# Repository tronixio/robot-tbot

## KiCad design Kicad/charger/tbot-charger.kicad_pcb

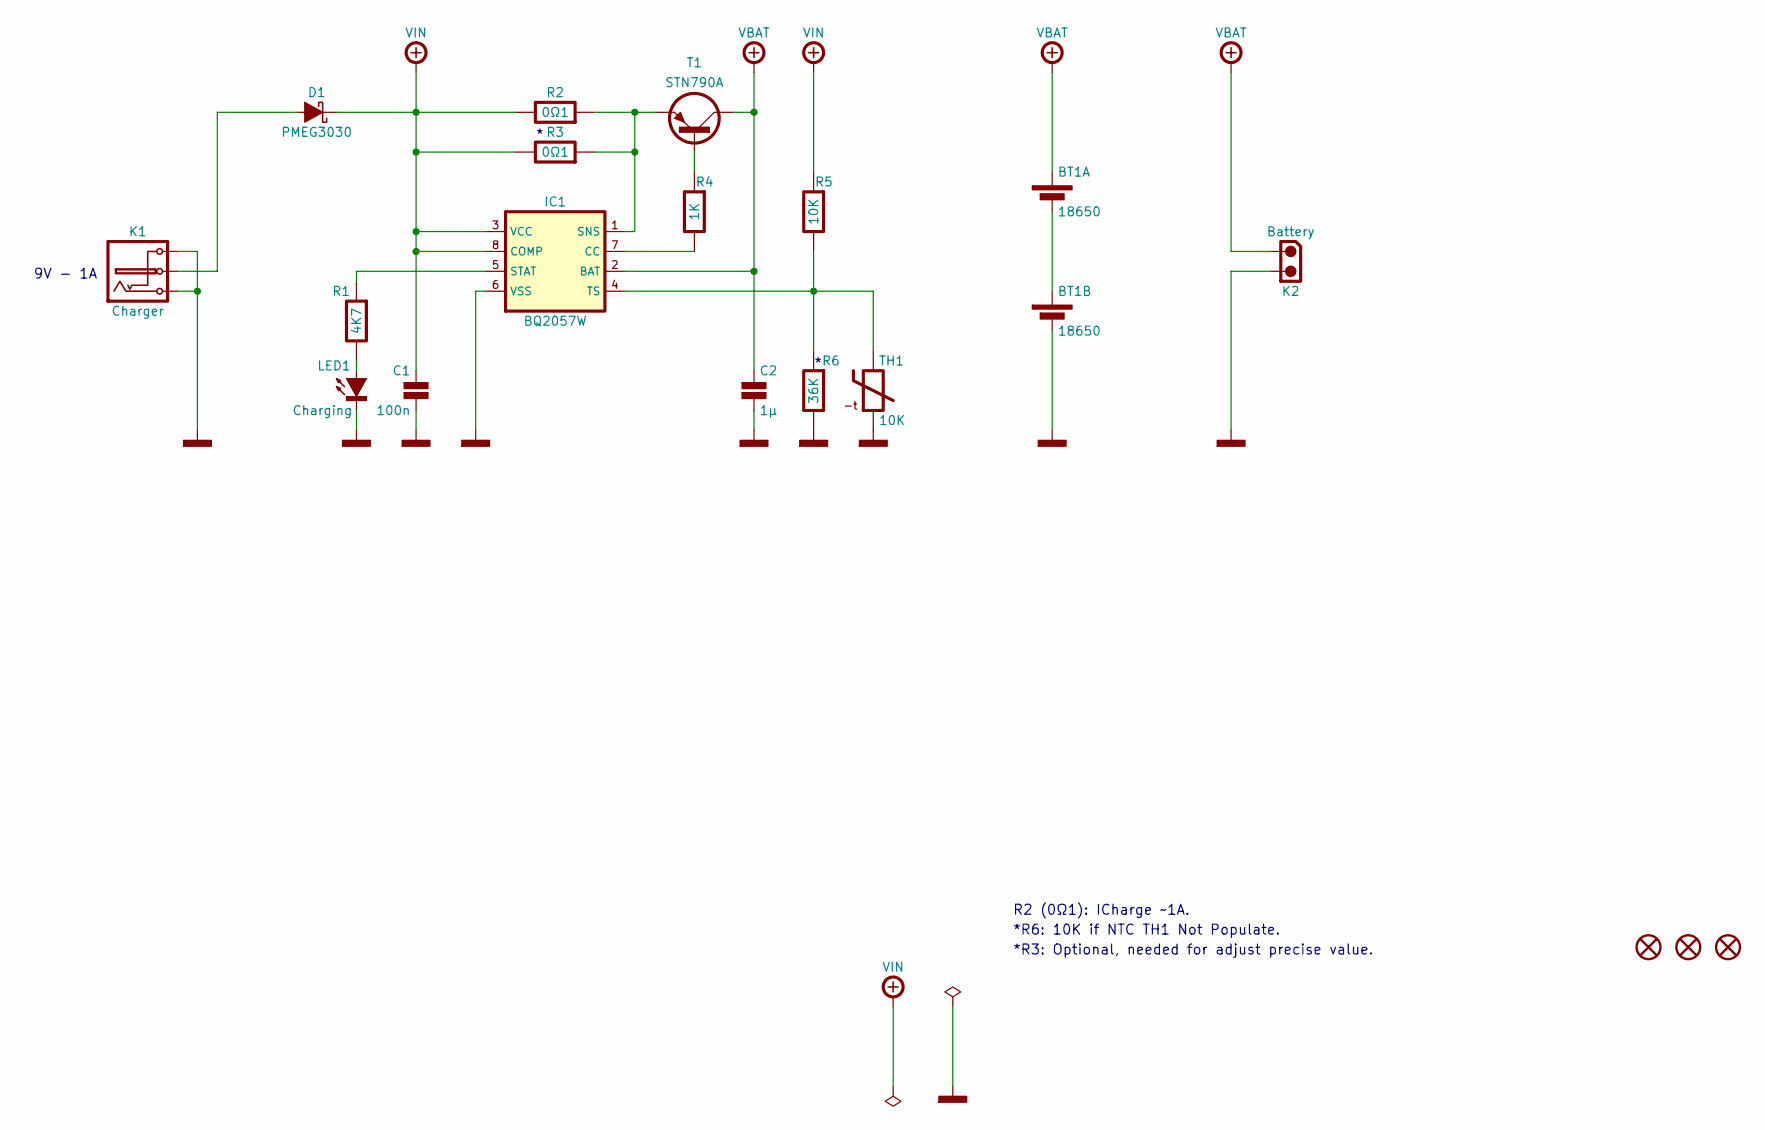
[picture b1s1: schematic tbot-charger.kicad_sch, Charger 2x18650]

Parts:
BT1: 18650; KEYSTONE-1049; MOUSER 534-1049
C1: 100n; CAPACITOR-1206
C2: 1µ; CAPACITOR-1206
D1: PMEG3030; SOD-128; MOUSER 771-PMEG3030EP115
H1, H2, H3: MOUNTING-HOLE-MASK-3MM; M3-MASK
IC1: BQ2057W; SOIC-08; MOUSER 595-BQ2057WSN
K1: Charger; CUI-PJ-102AH; MOUSER 490-PJ-102AH
K2: Battery; MOLEX-22057025; MOUSER 538-22-05-7025
LED1: Charging; LED-1206; MOUSER 604-APTR3216-VFX
R1: 4K7; RESISTOR-1206
R2, R3: 0Ω1; RESISTOR-1210
R4: 1K; RESISTOR-1206
R5: 10K; RESISTOR-1206
R6: 36K; RESISTOR-1206
T1: STN790A; SOT-223-3; MOUSER 511-STN790A
TH1: 10K; THERMISTOR; MOUSER 594-NTCLE213E3103FL

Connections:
GND: BT1.3 (-), C1.2, C2.2, IC1.6 (VSS), K1.2, K1.3, K2.2, LED1.1 (K), R6.1, TH1.2
unnamed: BT1.1 (-), BT1.4 (+)
unnamed: D1.2 (A), K1.1
unnamed: IC1.1 (SNS), R2.2, R3.2, T1.3 (E)
unnamed: IC1.4 (TS), R5.1, R6.2, TH1.1
unnamed: IC1.5 (STAT), R1.2
unnamed: IC1.7 (CC), R4.1
unnamed: LED1.2 (A), R1.1
unnamed: R4.2, T1.1 (B)
VBAT: BT1.2 (+), C2.1, IC1.2 (BAT), K2.1, T1.2 (C)
VIN: C1.1, D1.1 (C), IC1.3 (VCC), IC1.8 (COMP), R2.1, R3.1, R5.2

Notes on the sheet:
R2 (0Ω1): ICharge ~1A.
*R3: Optional, needed for adjust precise value.
9V - 1A
*R6: 10K if NTC TH1 Not Populate.

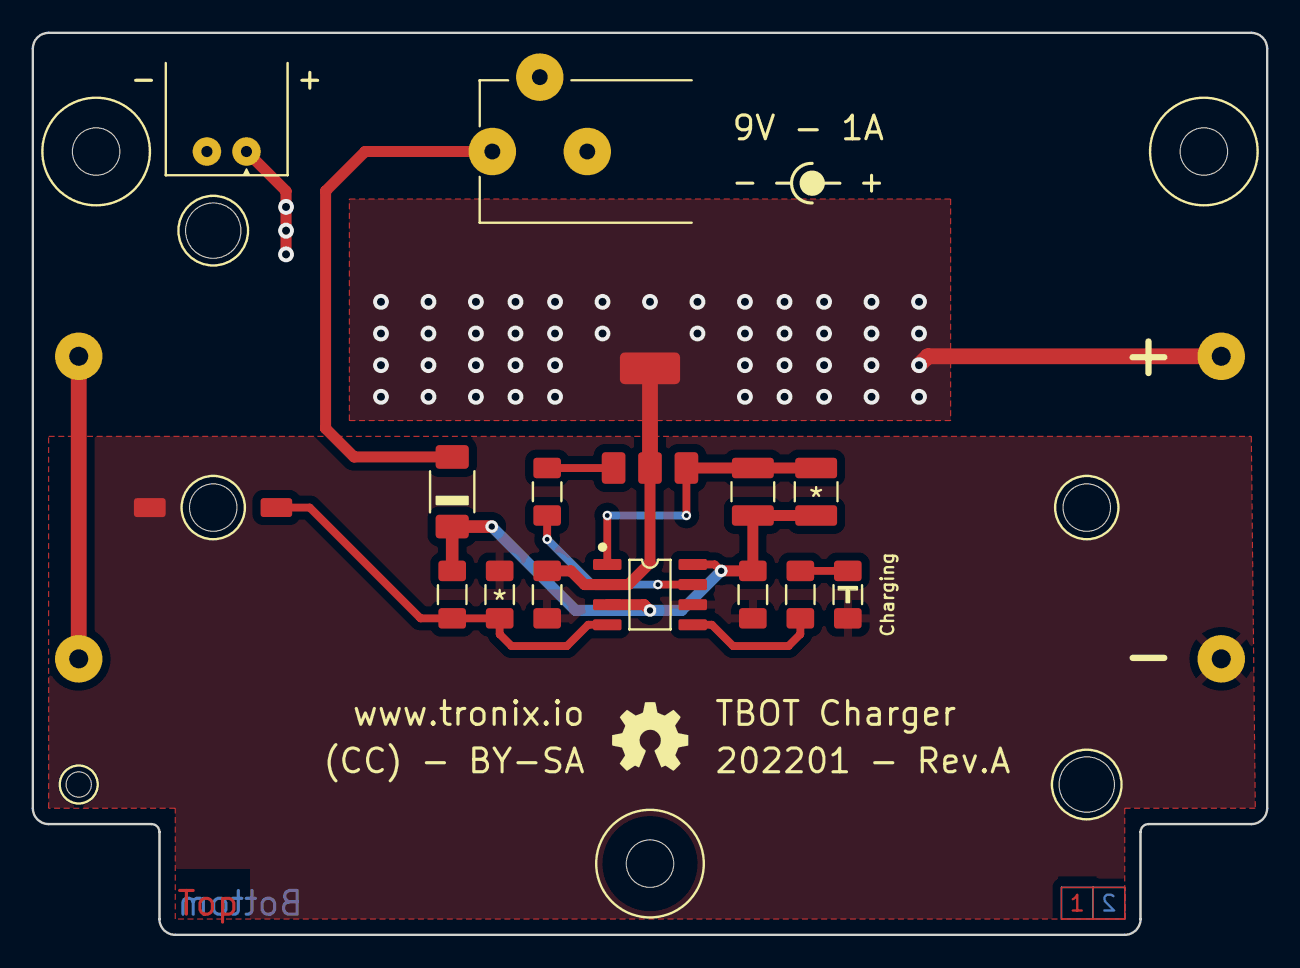
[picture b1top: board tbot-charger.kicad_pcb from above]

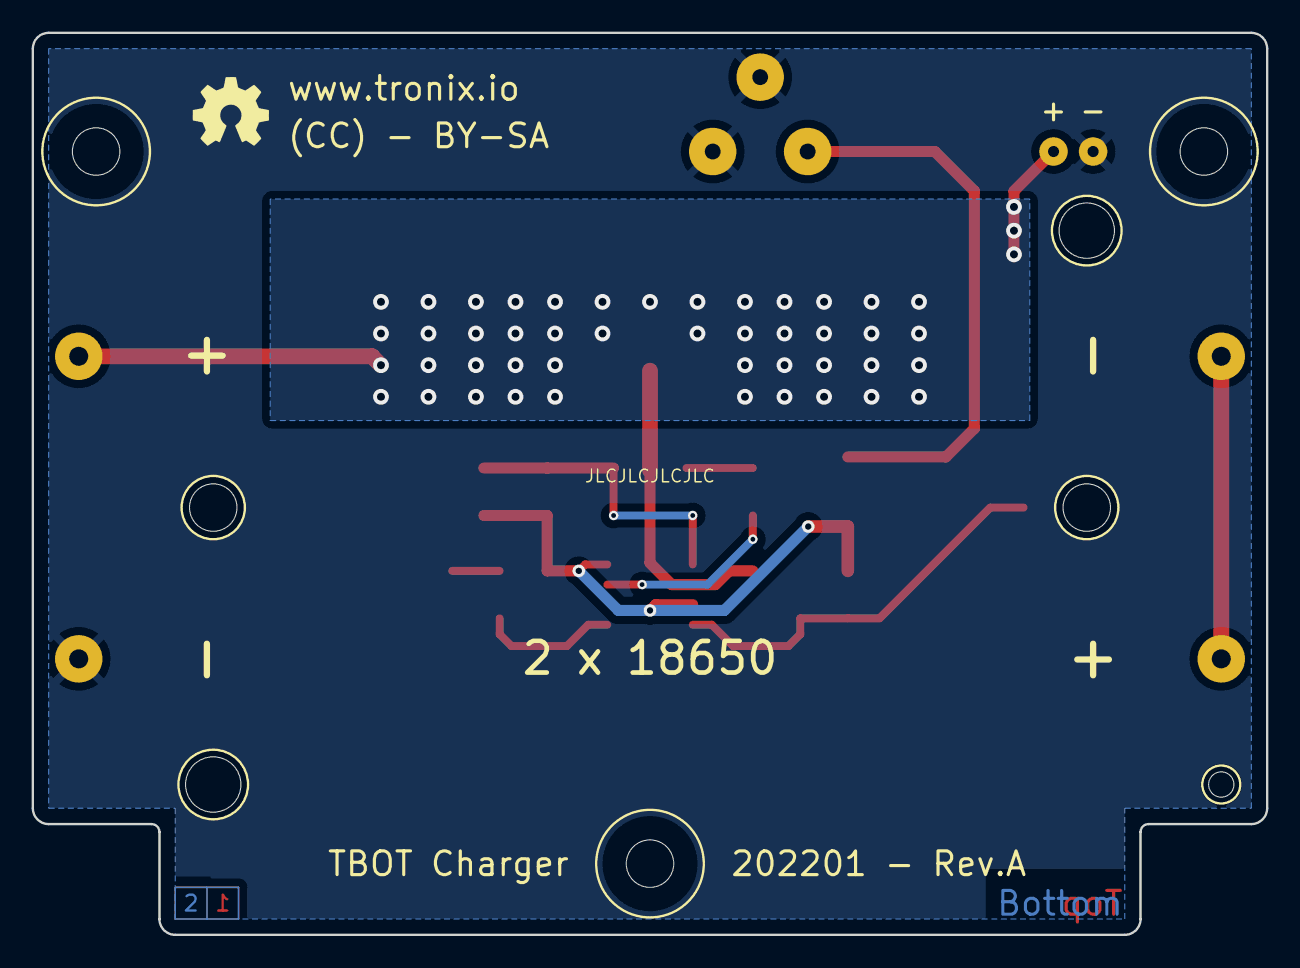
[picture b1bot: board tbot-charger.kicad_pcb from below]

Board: 2 copper layers, 78.0 x 57.0 mm, 21 parts (5 on the bottom side), 11 nets.

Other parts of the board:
GB: LOGO; OSHW-5MM
GT: LOGO; OSHW-5MM

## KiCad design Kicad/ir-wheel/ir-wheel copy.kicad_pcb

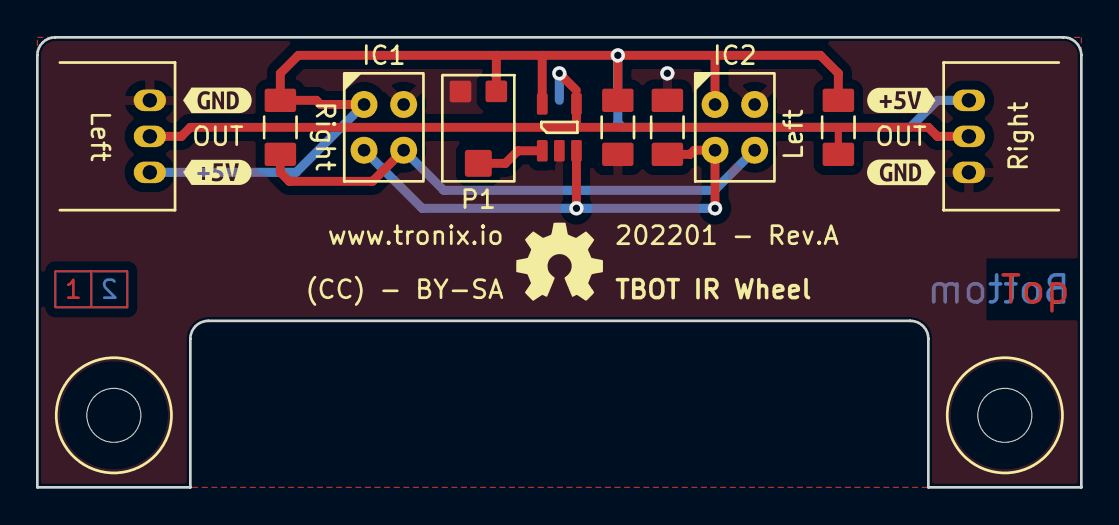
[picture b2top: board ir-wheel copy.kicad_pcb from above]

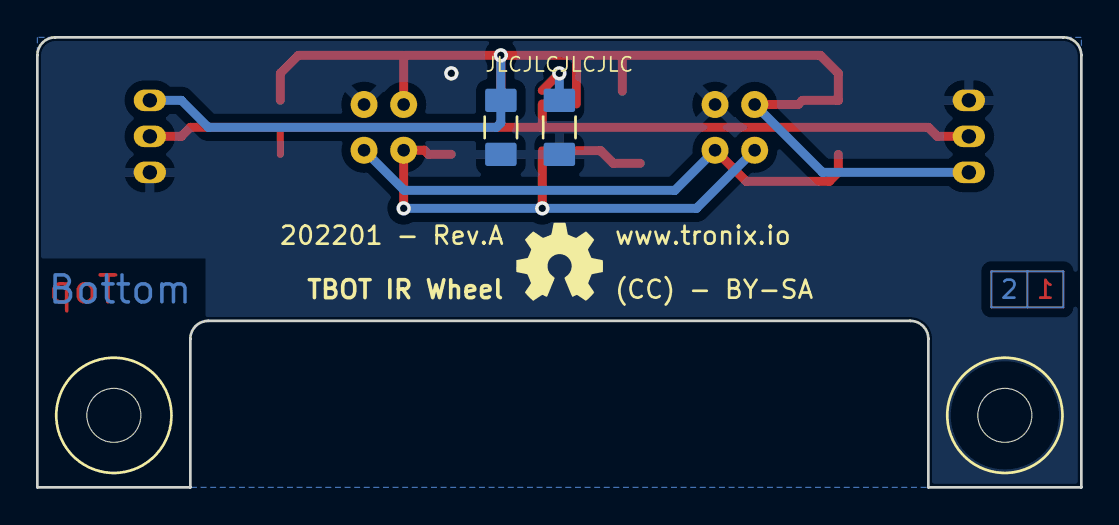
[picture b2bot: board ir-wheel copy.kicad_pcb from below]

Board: 2 copper layers, 58.0 x 25.0 mm, 20 parts (5 on the bottom side), 6 nets.

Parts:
C1: 100n; CAPACITOR-SMD-1206
C2: 1µ; CAPACITOR-SMD-1206
C3: 1n; CAPACITOR-SMD-1206
GB: LOGO; OSHW-5MM
GT: LOGO; OSHW-5MM
H1, H2: MOUNTING-HOLE-3MM-MASK
IC1, IC2: OPB606; OPB-606
K1: Right; MOLEX-532540370
K2: Left; MOLEX-532540370
P1: 200k; TC33X
R1: 220Ω; RESISTOR-SMD-1206
R2: 100k; RESISTOR-SMD-1206
R3: 10k; RESISTOR-SMD-1206
U1: MCP6541; SOT-23-5
kibuzzard-629B895E: G***; kibuzzard-629B895E
kibuzzard-629B896F: G***; kibuzzard-629B896F
kibuzzard-629B8952: G***; kibuzzard-629B8952
kibuzzard-629B8965: G***; kibuzzard-629B8965

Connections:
+5V: C1.1, C2.1, IC1.3 (COLLECTOR), IC2.3 (COLLECTOR), K1.1, K2.1, P1.1, R1.2, R3.2, U1.5 (VDD)
GND: C1.2, C2.2, C3.2, IC1.2 (CATHODE), IC2.2 (CATHODE), K1.3, K2.3, P1.3, R2.1, U1.2 (VSS)
unnamed: C3.1, K1.2, K2.2, R3.1, U1.4
unnamed: IC1.1 (ANODE), IC2.1 (ANODE), R1.1
unnamed: IC1.4 (EMITTER), IC2.4 (EMITTER), R2.2, U1.3 (-)
unnamed: P1.2, U1.1 (+)

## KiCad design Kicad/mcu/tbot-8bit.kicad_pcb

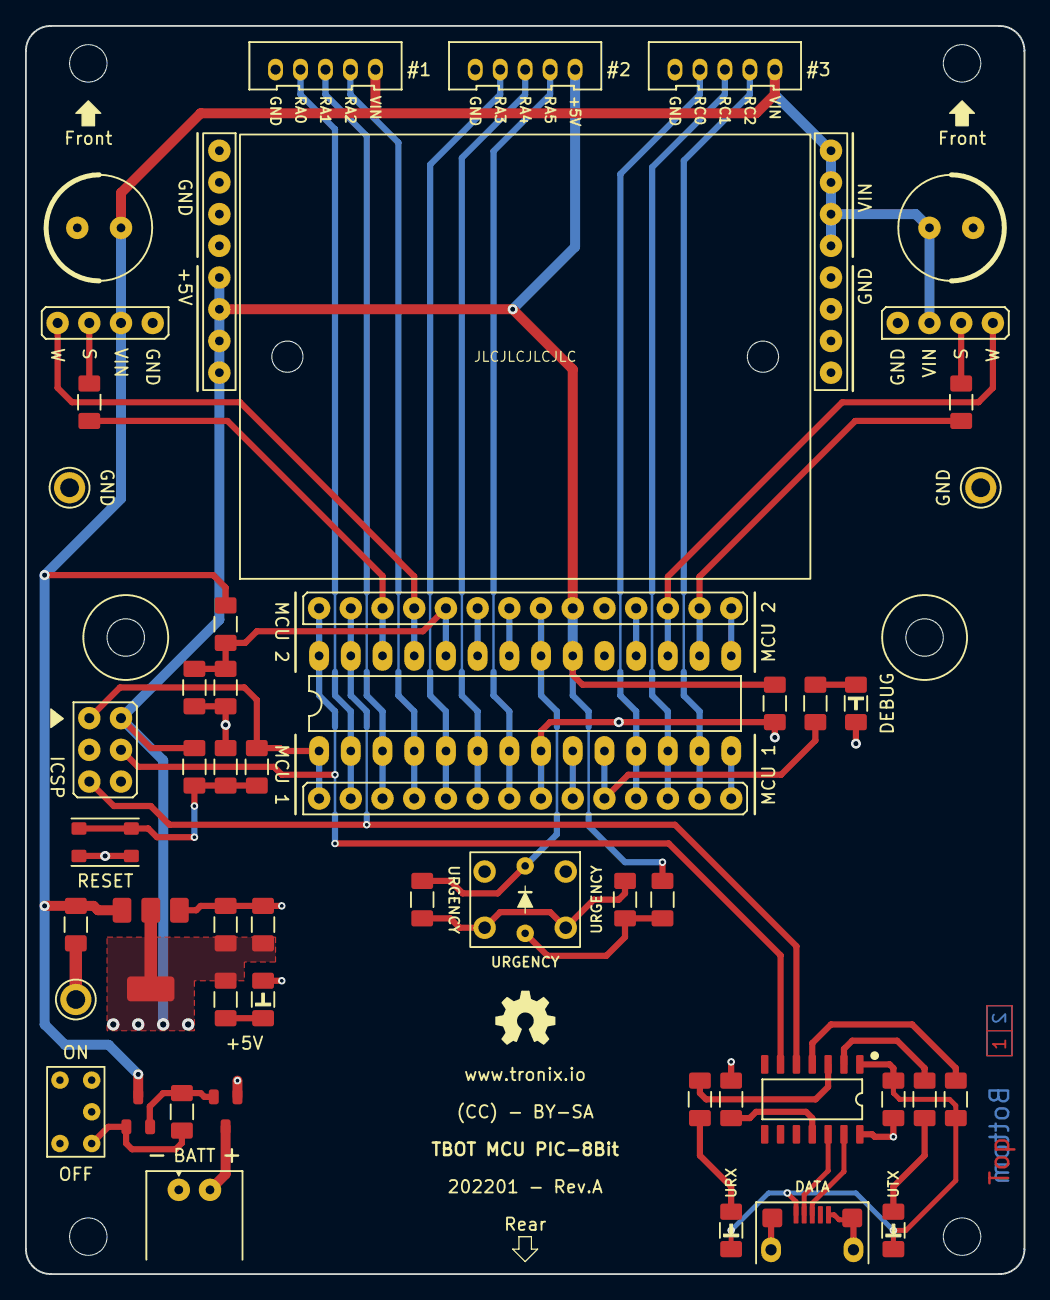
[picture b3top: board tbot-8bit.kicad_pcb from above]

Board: 2 copper layers, 80.0 x 100.0 mm, 59 parts (0 on the bottom side), 47 nets.

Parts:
BB401: BREADBOARD-170
C201, C203: 10µ; CAPACITOR-1206
C202, C204, C301, C302, C403: 100n; CAPACITOR-1206
C401, C404: 220µ/25V; CAPACITOR-ELECTROLYTIC-RADIAL-080-115-035
C402: 470n; CAPACITOR-1206
H101, H102, H103, H104, H105, H106: MOUNTING-HOLE-MASK-3MM; M3-MASK
IC201: TLV1117-50; SOT-223-3
IC301: PIC16F1778; DIP-28-W762-SOCKET
IC401: MCP2221A; SOIC-SL-14
K201: Battery; MOLEX-22057025
K301: MCU 1; HARWIN-M20-999144x
K302: ICSP; HARWIN-M20-998034x
K303: MCU 2; HARWIN-M20-999144x
K401: FRONT #1; MOLEX-532530570
K402: FRONT #2; MOLEX-532530570
K403: VIN; HARWIN-M20-782084x
K404: +5V; HARWIN-M20-782084x
K405: FRONT #3; MOLEX-532530570
K406: SERVO LEFT; HARWIN-M20-999044x
K407: USB/UART; FCI-USB-TYPE-B-MICRO-THT
K408: SERVO RIGHT; HARWIN-M20-999044x
LED201: Power; LED-1206
LED401: Debug; LED-1206
LED402: URX; LED-1206
LED403: UTX; LED-1206
R201: 1M; RESISTOR-1206
R202, R404, R407, R409: 4K7; RESISTOR-1206
R203: 7K5; RESISTOR-1206
R204, R301, R406: 10K; RESISTOR-1206
R302: 1K; RESISTOR-1206
R401, R405, R408: 220Ω; RESISTOR-1206
R402: 150Ω; RESISTOR-1206
R403: 330Ω; RESISTOR-1206
S201: Power; E-SWITCH-200USPXT1A1M2RE
S301: Reset; ALPS-SKRPAC
S401: EMERGENCY; E-SWITCH-TL1240XQ1JXXX
T201, T202: DMP2305U; SOT-23-3
TP201, TP202, TP203: GND; KEYSTONE-5006

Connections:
+5V: C202.1, C203.1, C302.1, IC201.2 (VO), IC301.20 (VDD), K302.2 (VDD), K303.9, K402.1, K404.1, K404.2, K404.3, K404.4, R202.2, R301.2, R401.2
/HID/D+: IC401.13 (D+), K407.3 (D+)
/HID/D-: IC401.12 (D-), K407.2 (D-)
/HID/RA0: IC301.2 (RA0), K301.2, K401.4
/HID/RA1: IC301.3 (RA1), K301.3, K401.3
/HID/RA2: IC301.4 (RA2), K301.4, K401.2
/HID/RA3: IC301.5 (RA3), K301.5, K402.4
/HID/RA4: IC301.6 (RA4/VCAP), K301.6, K402.3
/HID/RA5: IC301.7 (RA5), K301.7, K402.2
/HID/RA6/LED: IC301.10 (RA6/CLKO), K301.10, R404.2
/HID/RB0/EMERGENCY: IC301.21 (RB0), K303.8, R403.2, S401.5 (C)
/HID/RB4/WHEEL_L: IC301.25 (RB4), K303.4, K406.4
/HID/RB5/SERVO_L: IC301.26 (RB5), K303.3, R405.1
/HID/RB6/PGC/UTX: IC301.27 (PGC/RB6), IC401.5 (URx), K302.5 (PGC), K303.2
/HID/RB7/PGD/URX: IC301.28 (PGD/RB7), IC401.6 (UTx), K302.4 (PGD), K303.1
/HID/RC0: IC301.11 (RC0), K301.11, K405.4
/HID/RC1: IC301.12 (RC1), K301.12, K405.3
/HID/RC2: IC301.13 (RC2), K301.13, K405.2
/HID/RC5/SERVO_R: IC301.16 (RC5), K303.13, R408.1
/HID/RC6/WHEEL_R: IC301.17 (RC6), K303.12, K408.4
/MCU/RB3/BATTERY_SENSE: C204.1, IC301.24 (RB3), K303.5, R203.1, R204.2
GND: C201.2, C202.2, C203.2, C204.2, C301.2, C302.2, C401.2, C402.2, C403.2, C404.2, IC201.1 (GND), IC301.8 (VSS), IC301.19 (VSS), IC401.14 (VSS), K201.1, K301.8, K302.3 (GND), K303.10, K401.5, K402.5, K403.5, K403.6, K403.7, K403.8, K404.5, K404.6, K404.7, K404.8, K405.5, K406.1, K407.5 (GND), K407.6 (SHIELD), K408.1, LED201.1 (K), LED401.1 (K), R204.1, S201.2, S301.1, S301.2, S401.1, S401.2, T201.1 (G), TP201.1, TP202.1, TP203.1
unnamed: C301.1, R301.1, R302.2, S301.3, S301.4
unnamed: C402.1, IC401.11 (VUSB)
unnamed: IC401.2 (GP0), R409.1
unnamed: IC401.3 (GP1), R407.1
unnamed: IC401.4 (~RESET), R406.1
unnamed: K406.3, R405.2
unnamed: K408.3, R408.2
unnamed: LED201.2 (A), R202.1
unnamed: LED401.2 (A), R404.1
unnamed: LED402.1 (K), R407.2
unnamed: LED403.1 (K), R409.2
unnamed: R201.1, S201.3, T202.1 (G)
unnamed: R201.2, T201.2 (S), T202.2 (S)
unnamed: R401.1, R402.2, S401.6 (A)
unnamed: R402.1, R403.1, S401.3, S401.4
RA7: IC301.9 (RA7/CLKI), K301.9
RB1: IC301.22 (RB1), K303.7
RB2: IC301.23 (RB2), K303.6
RC3: IC301.14 (RC3), K301.14
RC4: IC301.15 (RC4), K303.14
RC7: IC301.18 (RC7), K303.11
VBAT: K201.2, T201.3 (D)
VIN: C201.1, C401.1, C404.1, IC201.3 (VI), K401.1, K403.1, K403.2, K403.3, K403.4, K405.1, K406.2, K408.2, R203.2, T202.3 (D)
VUSB: C403.1, IC401.1 (VDD), K407.1 (VBUS), LED402.2 (A), LED403.2 (A), R406.2
~MCLR: IC301.1 (RE3/~MCLR), K301.1, K302.1 (~MCLR), R302.1
